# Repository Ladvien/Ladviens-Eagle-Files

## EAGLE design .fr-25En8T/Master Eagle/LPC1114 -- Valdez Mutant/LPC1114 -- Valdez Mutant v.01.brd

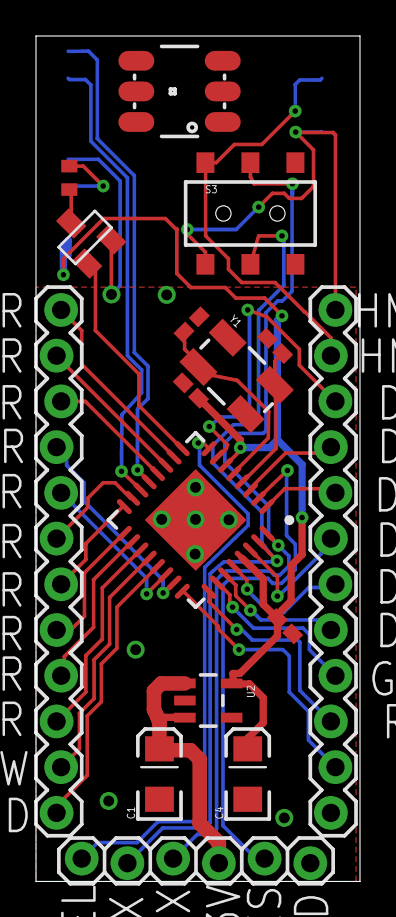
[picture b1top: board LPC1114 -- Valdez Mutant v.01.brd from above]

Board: 2 copper layers, 18.0 x 47.0 mm, 17 parts (1 on the bottom side), 37 nets.

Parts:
C1, C4: 10uF; EIA3216
C2, C3, C5, C6: 6PF; C0402K
JP1, JP2: M12LOCK; 1X12_LOCK
JP3: 1X06_LOCK
LED1: LED-TRICOLOR-5050NO_IC; LED-TRICOLOR-5050
Q1: BSS138; SOT23
R2: 1k; R0402
S3: DPDT; AYZ0202
U1: HVQFN33-7X7
U2: V_REG_LDOSMD; SOT23-5
U$1: HM-11
Y1: 12.5mhz; CRYSTAL-SMD-5X3

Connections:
3.3V: C4.A, C5.1, C6.1, U1.P$6, U1.P$29, U2.5, U$1.9
5V: C1.A, JP3.4, U2.1, U2.3
GND: C1.C, C2.1, C3.1, C4.C, C5.2, C6.2, JP3.6, Q1.2, U1.P$33, U2.2, U$1.12
HM-RX: JP2.12, S3.4, U$1.4
HM-TX: JP2.11, S3.1, U$1.2
HM_CONN: U1.P$13, U$1.16
HM_KEY: U1.P$14, U$1.15
IO20: JP2.8, U1.P$1
IO_00_RES: JP3.5, U1.P$2
IO_01: JP2.9, U1.P$3
IO_02_SEL: JP3.1, U1.P$8
IO_03: Q1.1, U1.P$9
IO_05-SDA: JP1.11, U1.P$11
IO_06: JP1.7, U1.P$15
IO_07: JP1.6, U1.P$16
IO_08: JP1.5, U1.P$17
IO_08-SCL: JP1.12, U1.P$10
IO_09: JP1.4, U1.P$18
IO_10: JP1.8, U1.P$22
IO_010: JP1.3, U1.P$19
IO_11: JP1.9, U1.P$23
IO_011: JP1.1, U1.P$21
IO_12: JP2.2, U1.P$24
IO_13: JP2.3, U1.P$25
IO_14: JP2.4, U1.P$26
IO_15: JP2.7, U1.P$30
IO_18: JP2.10, U1.P$7
IO_19: JP1.10, U1.P$12
IO_32: JP2.6, U1.P$28
IO_110: JP1.2, U1.P$20
IO_111: JP2.5, U1.P$27
unnamed: Q1.3, R2.2
unnamed: R2.1, U$1.11
unnamed: C3.2, U1.P$4, Y1.3
unnamed: C2.2, U1.P$5, Y1.1
RX: JP3.3, S3.2, U1.P$32
TX: JP3.2, S3.5, U1.P$31

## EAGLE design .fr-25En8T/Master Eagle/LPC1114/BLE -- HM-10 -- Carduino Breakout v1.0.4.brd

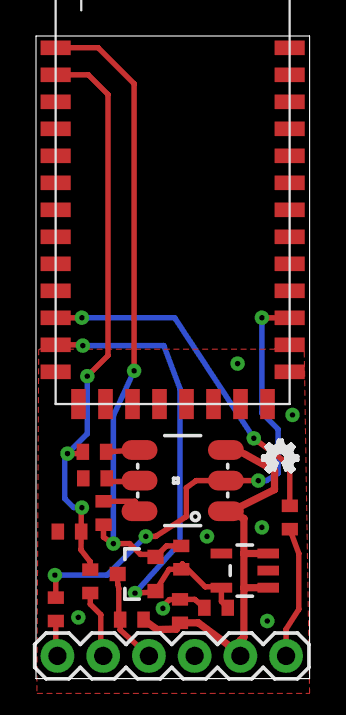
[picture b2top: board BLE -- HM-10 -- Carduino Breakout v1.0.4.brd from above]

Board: 2 copper layers, 15.2 x 35.7 mm, 19 parts (1 on the bottom side), 14 nets.

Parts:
BSS138: MOSFET-NCHANNELSMD; SOT23-3
C1, C2: 1uF; C0402
JP1: 1X06
LED1: LED-TRICOLOR-5050NO_IC; LED-TRICOLOR-5050
R1, R2, R7: 470; R0402
R3, R5, R6: 10k; R0402
R4: 20k; R0402
R8, R9: 10K; R0402
U1: V_REG_LDOSMD; SOT23-5
U$1: BLE-HM-10
U$2, U$3, U$4: OSHW_FILLX70_NOTEXT

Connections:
3_3V: BSS138.1, C2.1, R6.2, U1.5, U$1.3.3V
5V: C1.1, JP1.5, LED1.1, LED1.3, R5.2, U1.1, U1.3
CONN_PIN: LED1.2, R8.2, U$1.PIO1
CONN_STAT: JP1.1, R8.1
GND: C1.2, C2.2, JP1.4, R4.2, R7.1, U1.2, U$1.GND1, U$1.GND2, U$1.GND3, U$1.GND4
HVTX->LVRX: R2.1, R3.2, R4.1, U$1.UART_RX
LVRX->HVTX: BSS138.2, R1.1, R6.1, U$1.UART_TX
unnamed: LED1.6, R1.2
unnamed: LED1.4, R2.2
unnamed: LED1.5, R7.2
RES: R9.1, U$1.RESET
RES_C: JP1.6, R9.2
RX: JP1.2, R3.1
TX: BSS138.3, JP1.3, R5.1

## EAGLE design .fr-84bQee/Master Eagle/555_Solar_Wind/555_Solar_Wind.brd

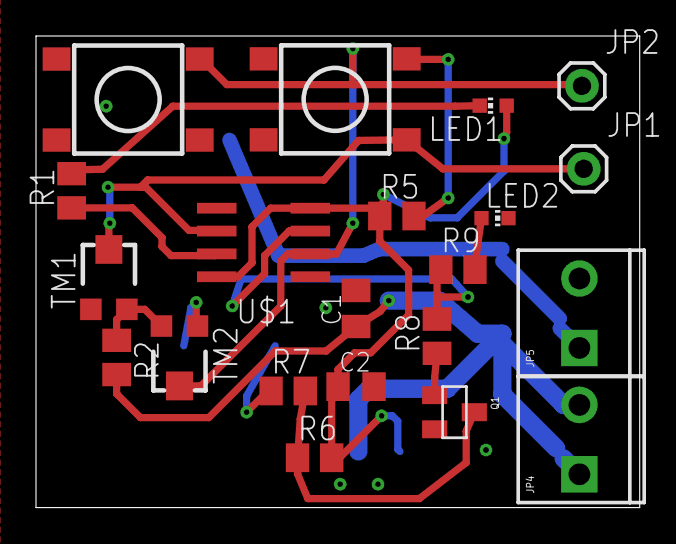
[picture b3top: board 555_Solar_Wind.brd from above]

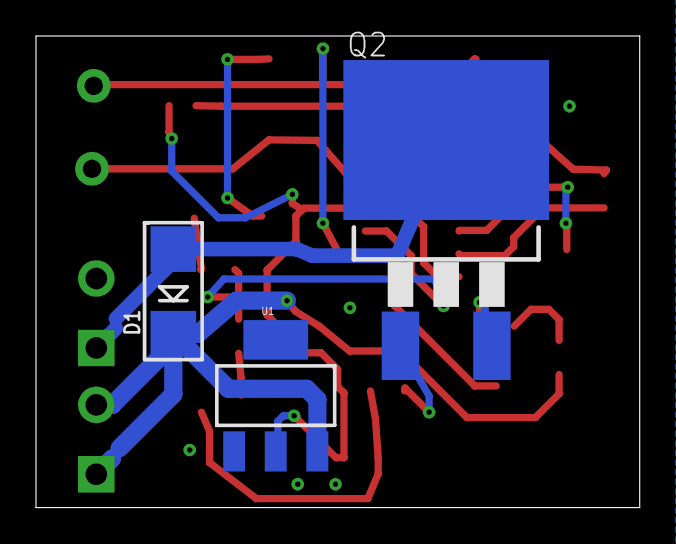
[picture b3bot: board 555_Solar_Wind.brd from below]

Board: 2 copper layers, 33.5 x 26.2 mm, 24 parts (3 on the bottom side), 15 nets.

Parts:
C1: .33uF; C0805K
C2: .1uF; C0805K
D1: S1BB; SMADIODE
JP1, JP2: M01PTH; 1X01
JP4, JP5: M023.5MM_LOCK; SCREWTERMINAL-3.5MM-2_LOCK
LED1, LED2: CHIP-LED0603
Q1: MMBT2222A; SOT23
Q2: FQB33N10L; D2PACK
R1, R8, R9: 1k; M0805
R2, R5, R6: 330 Ohm; M0805
R7: 100 Ohm; M0805
S1, S2: SWITCH-MOMENTARY-2; TACTILE_SWITCH_TALL
TM1, TM2: TC33X
U1: 5V; SOT223
U$1: NE555_SOIC; SO08

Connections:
5V: C2.1, LED1.A, R5.1, R6.2, U1.2, U$1.4, U$1.8
12V: C1.1, D1.C, JP4.1, JP4.2, R2.2, U1.3
GATE: Q2.1, R7.1
GND: C1.2, C2.2, JP5.2, LED2.C, Q1.2, Q2.3, S2.A2, TM1.1, TM2.1, U1.1, U$1.1
unnamed: LED2.A, R9.2
unnamed: R2.1, TM1.3, TM2.3
unnamed: JP1.1, S1.A2, TM1.2, U$1.6
unnamed: JP2.1, S2.B2, TM2.2, U$1.2
unnamed: R5.2, S1.B2
unnamed: Q1.3, R6.1, R7.2
unnamed: LED1.C, R1.2
unnamed: R1.1, U$1.7
unnamed: R8.2, R9.1, U$1.3
unnamed: Q1.1, R8.1
RELAY_1: D1.A, JP5.1, Q2.2

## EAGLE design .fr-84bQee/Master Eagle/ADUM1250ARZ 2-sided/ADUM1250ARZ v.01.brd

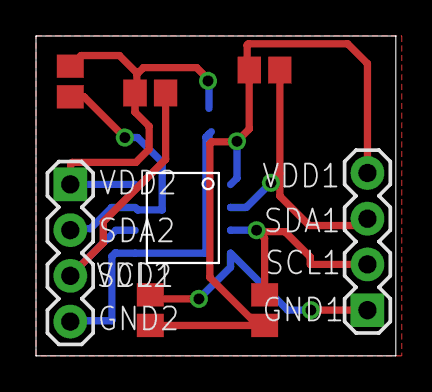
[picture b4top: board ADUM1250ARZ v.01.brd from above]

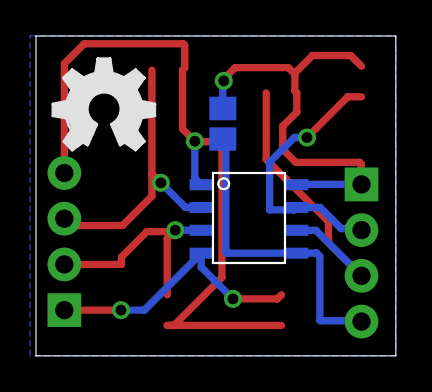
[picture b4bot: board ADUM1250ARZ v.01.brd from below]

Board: 2 copper layers, 20.0 x 17.8 mm, 10 parts (3 on the bottom side), 8 nets.

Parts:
C1, C2: .1uF; C0805
JP1, JP2: 1X04
R1, R2, R3, R4: 4.7k; R0805
U$1: ADUM1250ARZ
U$2: OSHW_FILLX200_NOTEXT

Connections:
GND1: C1.2, JP1.1, U$1.GND1
GND2: C2.2, JP2.4, U$1.GND2
SCL1: JP1.2, R1.1, U$1.SCL1
SCL2: JP2.3, R3.1, U$1.SCL2
SDA1: JP1.3, R2.1, U$1.SDA1
SDA2: JP2.2, R4.1, U$1.SDA2
VDD1: C1.1, JP1.4, R1.2, R2.2, U$1.VDD1
VDD2: C2.1, JP2.1, R3.2, R4.2, U$1.VDD2

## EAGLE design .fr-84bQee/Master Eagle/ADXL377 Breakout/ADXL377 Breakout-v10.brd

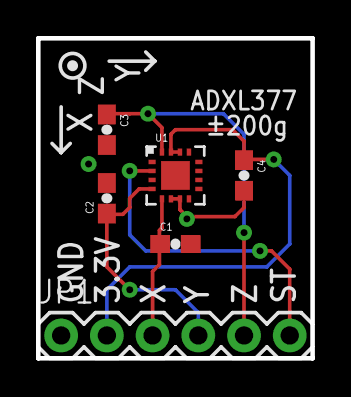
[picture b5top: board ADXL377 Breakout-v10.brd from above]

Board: 2 copper layers, 15.2 x 17.8 mm, 7 parts (1 on the bottom side), 6 nets.

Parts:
C1, C2, C3: 10nF; 0603-CAP
C4: 0.1uF; 0603-CAP
JP1: 1X06
LOGO2: OSHW-LOGOS; OSHW-LOGO-S
U1: ADXL377; LFCSP_LQ-16

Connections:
3.3V: C4.1, JP1.2, U1.14, U1.15
GND: C1.2, C2.2, C3.2, C4.2, JP1.1, U1.6, U1.7
ST: JP1.6, U1.2
X: C1.1, JP1.3, U1.5
Y: C2.1, JP1.4, U1.4
Z: C3.1, JP1.5, U1.16

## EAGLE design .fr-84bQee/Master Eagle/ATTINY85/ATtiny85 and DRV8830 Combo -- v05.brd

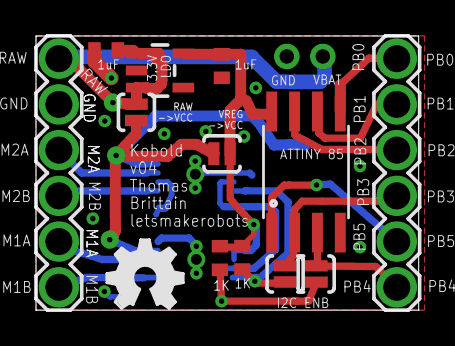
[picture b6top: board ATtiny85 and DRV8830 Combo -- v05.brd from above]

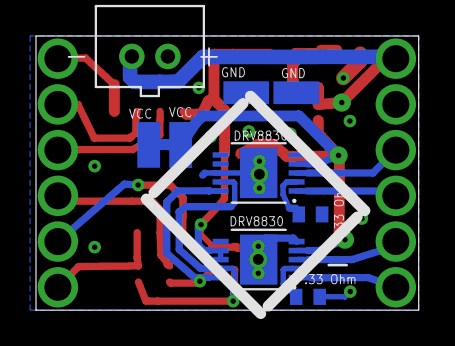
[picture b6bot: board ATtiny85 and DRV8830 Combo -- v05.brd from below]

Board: 2 copper layers, 21.3 x 15.2 mm, 22 parts (9 on the bottom side), 18 nets.

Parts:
1K: R3; R0402
C1, C2: 1uf; C0402
CN1: JST-PH-2-THM
PAD1, PAD2, PAD3, PAD4: SMD1,27-2,54
R1, R3: .33; R0402
R2: 1k; R0402
RAW: SOLDERJUMPERNO; SJ_2S-NO
SJ6, SJ7: SOLDERJUMPERNO; SJ_2S-NO
U1: V_REG_LDOSMD; SOT23-5
U2, U3: DRV8830; MSOP-10-GNDPAD
U$1, U$4: 1X6_SHORT_ROUND
U$2: ATTINY85; SO08-EIAJ
U$3: OSHW_FILLX150_NOTEXT
VREG: SOLDERJUMPERNO; SJ_2S-NO

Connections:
BAT_RAW: C1.1, CN1.2, RAW.1, U1.1, U1.3, U$4.1
GND: C1.2, C2.2, CN1.1, PAD1.1, PAD3.1, R1.1, R3.1, U1.2, U2.5, U2.GND, U3.5, U3.7, U3.8, U3.GND, U$2.4, U$4.2
M1_A: U2.3, U$4.5
M1_B: U2.1, U$4.6
M2_A: U3.3, U$4.3
M2_B: U3.1, U$4.4
unnamed: R1.2, U3.2
unnamed: R3.2, U2.2
PB0: U$1.1, U$2.5
PB1: U$1.2, U$2.6
PB2: U$1.3, U$2.7
PB3: SJ7.2, U$1.4, U$2.2
PB4: SJ6.2, U$1.6, U$2.3
PB5: U$1.5, U$2.1
SCL: R2.2, SJ7.1, U2.10, U3.10
SDA: 1K.2, SJ6.1, U2.9, U3.9
VCC: PAD2.1, PAD4.1, RAW.2, U2.4, U3.4, VREG.2
VREG: 1K.1, C2.1, R2.1, U1.5, U2.7, U2.8, U$2.8, VREG.1

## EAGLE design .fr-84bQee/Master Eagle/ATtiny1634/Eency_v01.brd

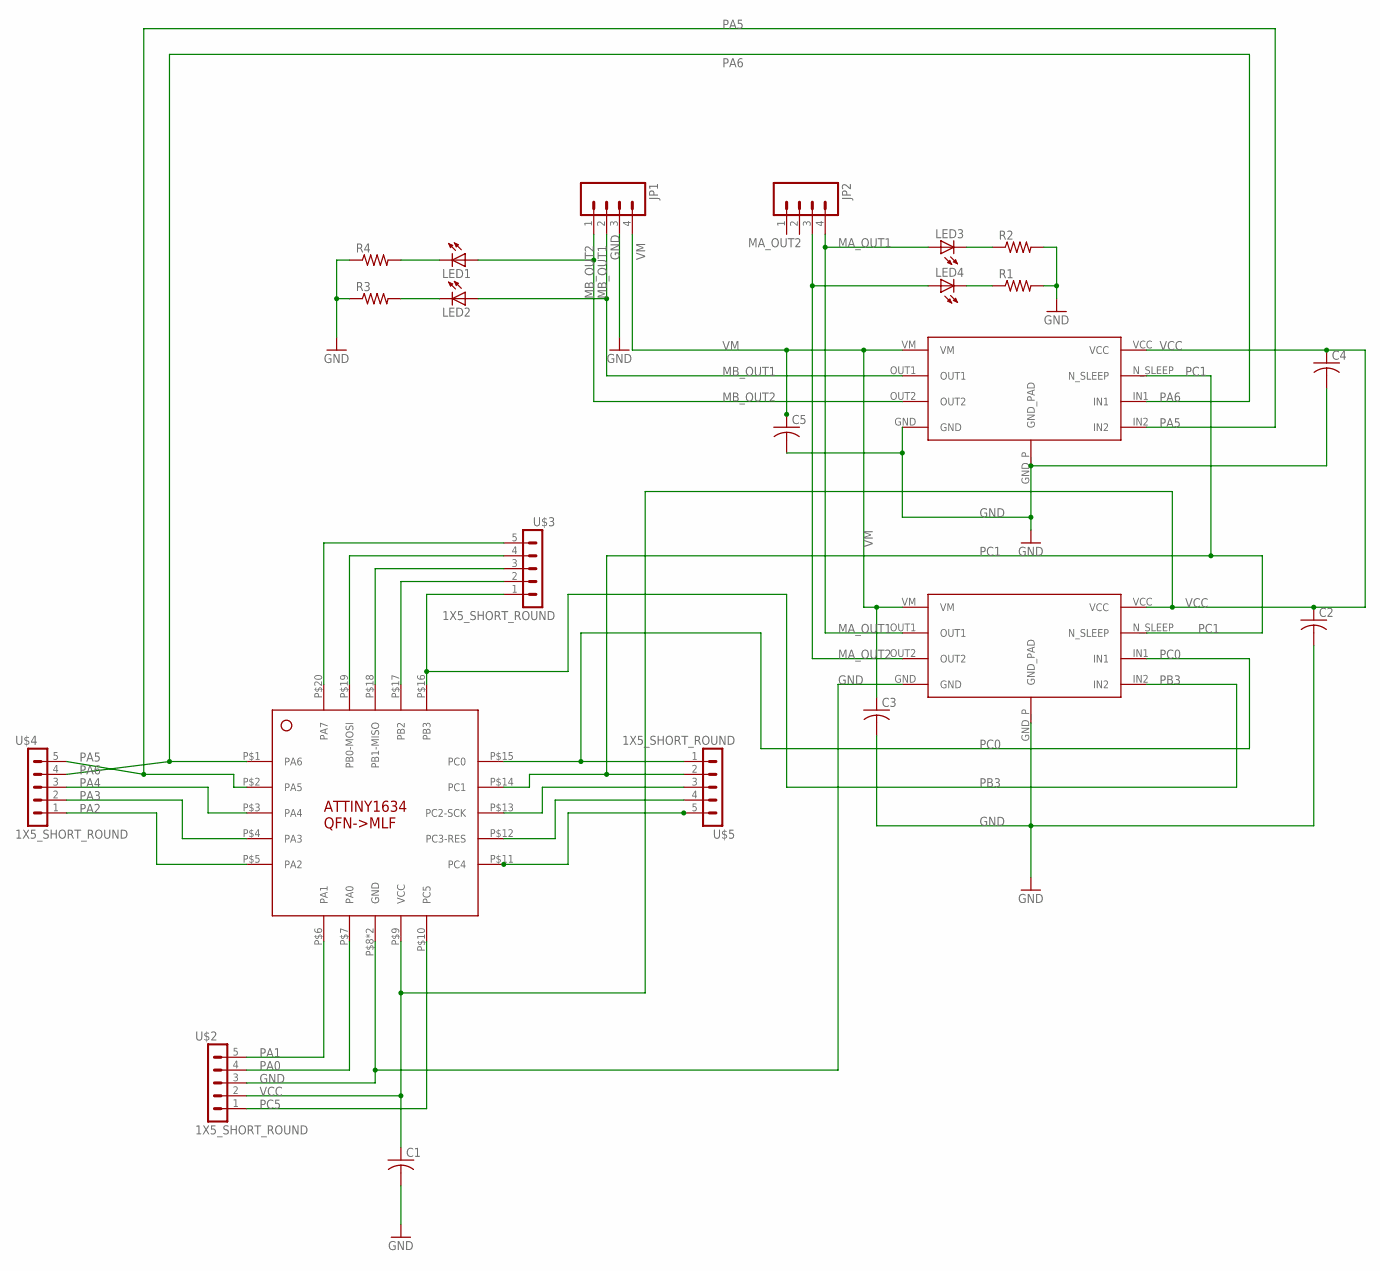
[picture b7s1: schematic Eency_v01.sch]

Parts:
C1, C2, C3, C4, C5: C-USC0402K; C0402K
JP1, JP2: M04PTH; 1X04
LED1, LED2, LED3, LED4: LEDSML0603; SML0603
R1, R2, R3, R4: R-US_R0402; R0402
U$1: ATTINY1634; MLF20/ATTINY13
U$2, U$3, U$4, U$5: 1X5_SHORT_ROUND
U$8, U$9: DRV8837; WSON-8

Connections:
GND: C1.2, C2.2, C3.2, C4.2, C5.2, JP1.3, R1.2, R2.2, R3.1, R4.1, U$1.P$8 (GND), U$1.P$21 (GND), U$2.3 (4), U$8.GND, U$8.GND_P (GND_PAD), U$9.GND, U$9.GND_P (GND_PAD)
MA_OUT1: JP2.4, LED3.A, U$8.OUT1
MA_OUT2: JP2.3, LED4.A, U$8.OUT2
MB_OUT1: JP1.2, LED2.A, U$9.OUT1
MB_OUT2: JP1.1, LED1.A, U$9.OUT2
unnamed: U$1.P$18 (PB1-MISO), U$3.3 (4)
unnamed: U$1.P$19 (PB0-MOSI), U$3.4 (5)
unnamed: LED3.C, R2.1
unnamed: LED4.C, R1.1
unnamed: LED1.C, R4.2
unnamed: LED2.C, R3.2
PA0: U$1.P$7 (PA0), U$2.4 (5)
PA1: U$1.P$6 (PA1), U$2.5 (6)
PA2: U$1.P$5 (PA2), U$4.1 (2)
PA3: U$1.P$4 (PA3), U$4.2 (3)
PA4: U$1.P$3 (PA4), U$4.3 (4)
PA5: U$1.P$2 (PA5), U$4.5 (6), U$9.IN2
PA6: U$1.P$1 (PA6), U$4.4 (5), U$9.IN1
PA7: U$1.P$20 (PA7), U$3.5 (6)
PB2: U$1.P$17 (PB2), U$3.2 (3)
PB3: U$1.P$16 (PB3), U$3.1 (2), U$8.IN2
PC0: U$1.P$15 (PC0), U$5.1 (2), U$8.IN1
PC1: U$1.P$14 (PC1), U$5.2 (3), U$8.N_SLEEP, U$9.N_SLEEP
PC2-SCK: U$1.P$13 (PC2-SCK), U$5.3 (4)
PC3-RES: U$1.P$12 (PC3-RES), U$5.4 (5)
PC4: U$1.P$11 (PC4), U$5.5 (6)
PC5: U$1.P$10 (PC5), U$2.1 (2)
VCC: C1.1, C2.1, C4.1, U$1.P$9 (VCC), U$2.2 (3), U$8.VCC, U$9.VCC
VM: C3.1, C5.1, JP1.4, U$8.VM, U$9.VM

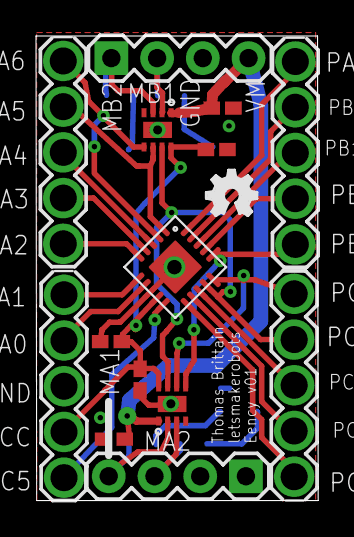
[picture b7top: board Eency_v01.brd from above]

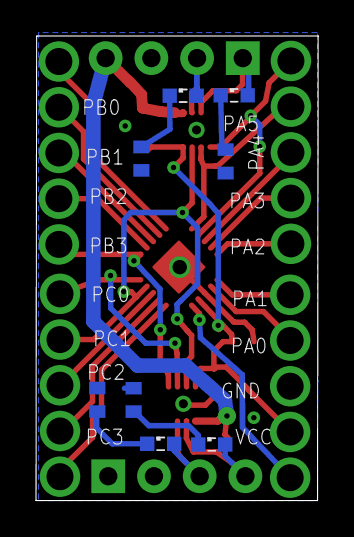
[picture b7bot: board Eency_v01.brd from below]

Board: 2 copper layers, 15.7 x 25.8 mm, 23 parts (8 on the bottom side), 29 nets.

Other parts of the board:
U$7: OSHW_FILLX100_NOTEXT

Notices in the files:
parts and their libraries:
microbuilder: This work is placed in the public domain, and may be freely used for commercial and non-commercial work with the following conditions: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
SparkFun-Connectors: Licensing: Creative Commons ShareAlike 4.0 International - https://creativecommons.org/licenses/by-sa/4.0
